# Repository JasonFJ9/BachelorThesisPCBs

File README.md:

# BachelorThesisPCBs
PCBs from Bachelor Thesis

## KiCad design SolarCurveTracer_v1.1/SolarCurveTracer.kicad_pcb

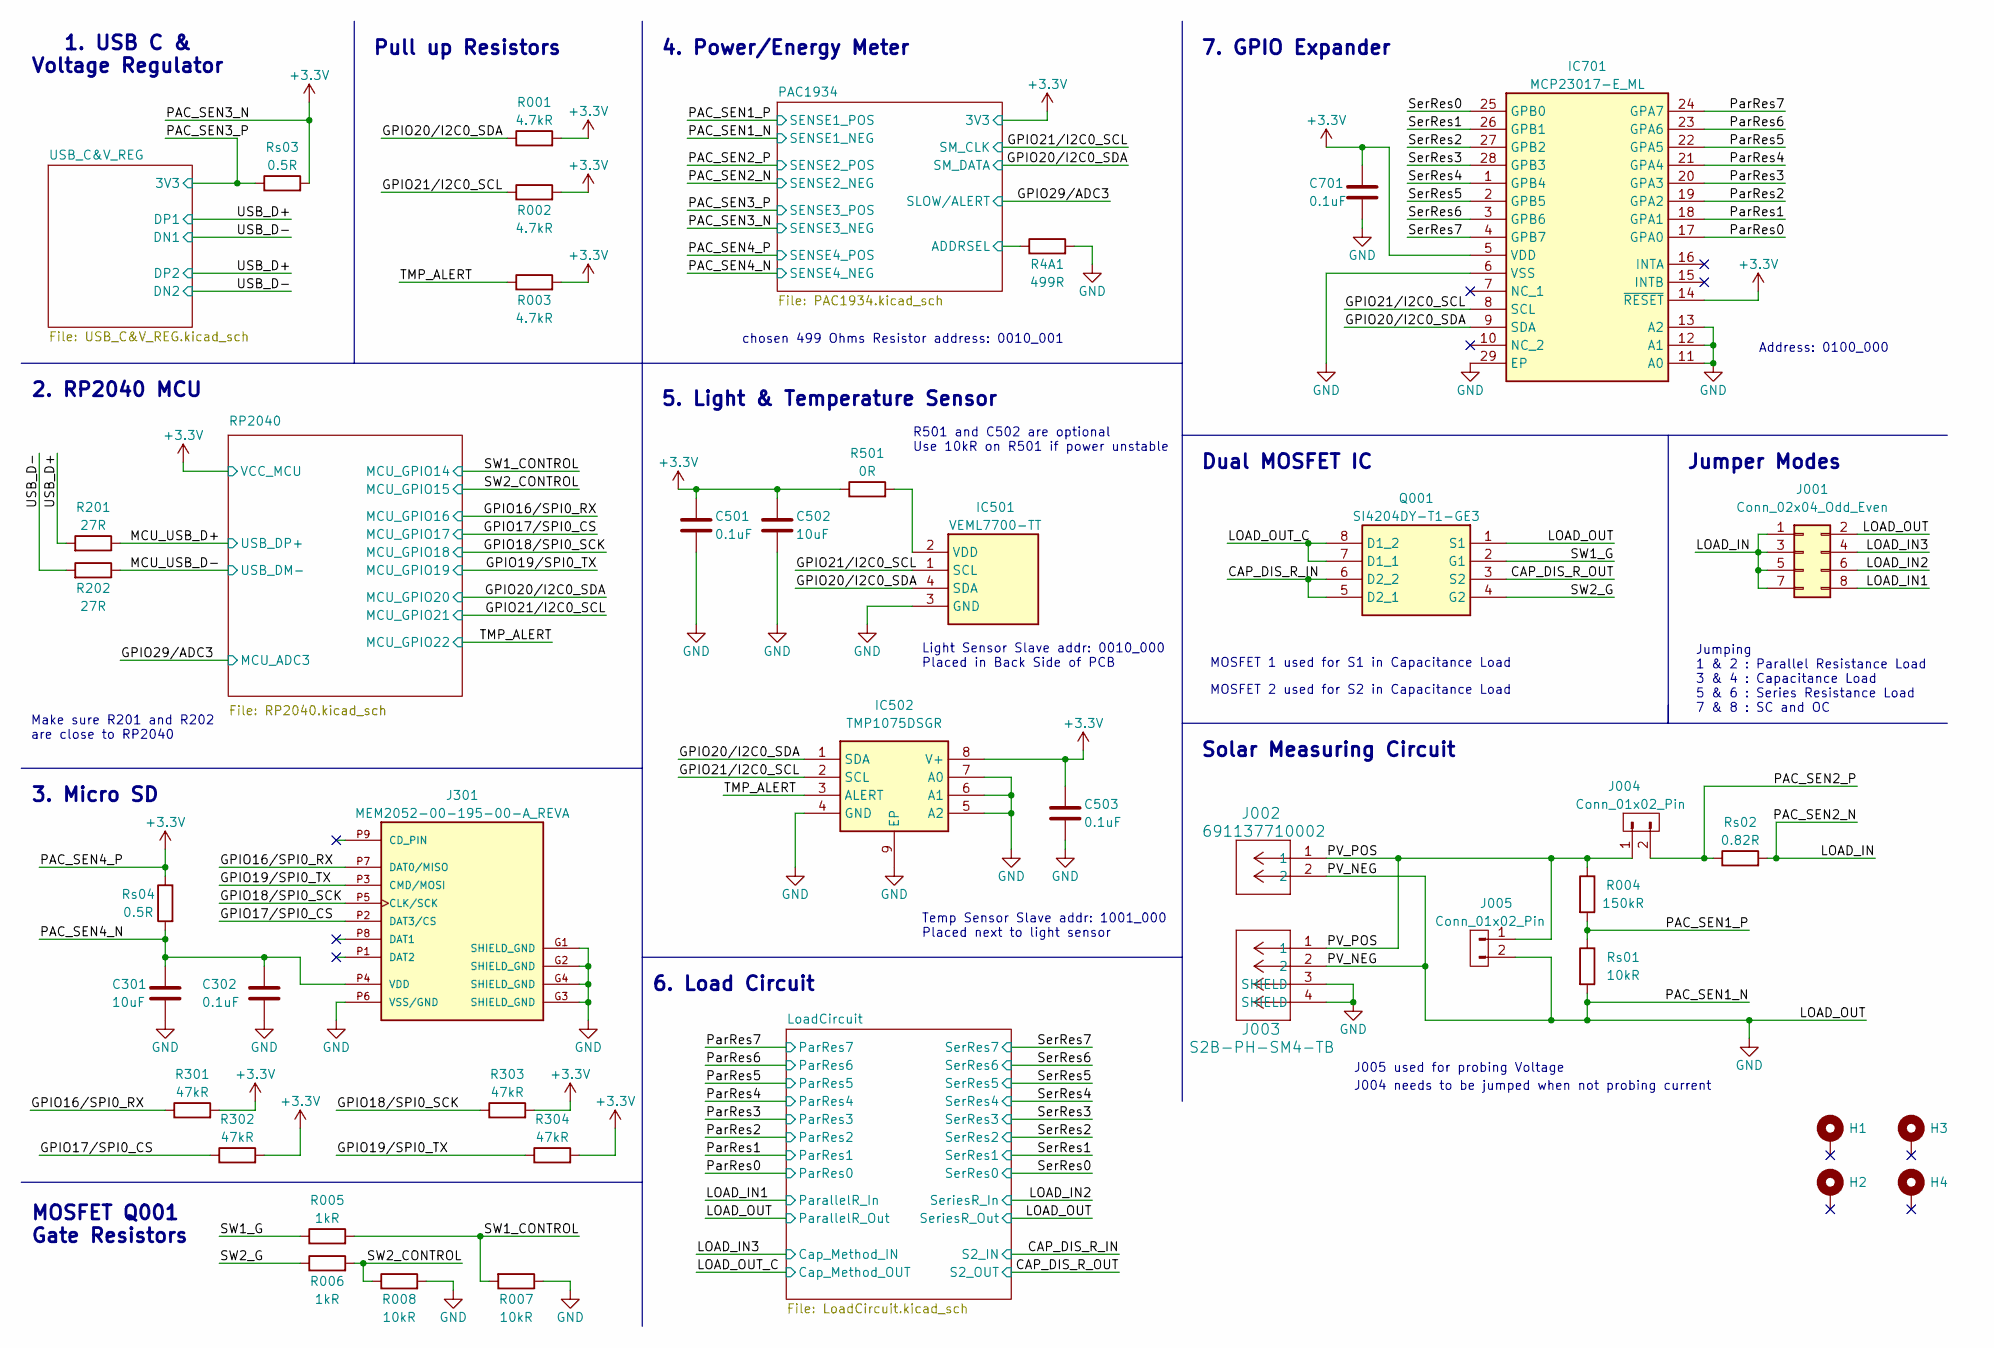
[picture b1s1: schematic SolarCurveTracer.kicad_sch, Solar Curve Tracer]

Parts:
C301, C502: 10uF; C_0603_1608Metric
C302, C501, C701: 0.1uF; C_0603_1608Metric
C503: 0.1uF; C_0402_1005Metric
H1, H2, H3, H4: MountingHole_Pad; MountingHole_3.2mm_M3_Pad
IC501: VEML7700-TT; VEML7700; Mouser Part Number 78-VEML7700-TT
IC502: TMP1075DSGR; SON50P200X200X80-9N; Mouser Part Number 595-TMP1075DSGR
IC701: MCP23017-E_ML; QFN65P600X600X100-29N-D; Mouser Part Number 579-MCP23017-E/ML
J001: Conn_02x04_Odd_Even; PinHeader_2x04_P2.54mm_Vertical
J002: 691137710002; CONN2_710002_WRE
J003: S2B-PH-SM4-TB; CONN_S2B-PH-SM4-TB_JST
J004, J005: Conn_01x02_Pin; PinHeader_1x02_P2.54mm_Vertical
J301: MEM2052-00-195-00-A_REVA; GCT_MEM2052-00-195-00-A_REVA; PARTREV A
Q001: SI4204DY-T1-GE3; SOIC127P600X175-8N; Mouser Part Number 781-SI4204DY-T1-GE3
R001, R002, R003: 4.7kR; R_0402_1005Metric
R004: 150kR; R_0603_1608Metric
R4A1: 499R; R_0603_1608Metric
R005, R006: 1kR; R_0402_1005Metric
R007, R008: 10kR; R_0402_1005Metric
R201, R202: 27R; R_0402_1005Metric
R301, R302, R303, R304: 47kR; R_0603_1608Metric
R501: 0R; R_0603_1608Metric
Rs01: 10kR; R_0805_2012Metric
Rs02: 0.82R; R_0805_2012Metric
Rs03, Rs04: 0.5R; R_0805_2012Metric

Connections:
+3.3V: C501.1, C502.1, C503.1, C701.1, IC502.8 (V+), IC701.5 (VDD), IC701.14 (~RESET), R001.2, R002.2, R003.2, R301.2, R302.2, R303.2, R304.2, R501.1, Rs03.2, Rs04.1; also elsewhere on the board
/CAP_DIS_R_IN: Q001.5 (D2_1), Q001.6 (D2_2); also elsewhere on the board
/CAP_DIS_R_OUT: Q001.3 (S2), Q001.7 (D1_1), Q001.8 (D1_2); also elsewhere on the board
/GPIO16/SPI0_RX: J301.P7 (DAT0/MISO), R301.1; also elsewhere on the board
/GPIO17/SPI0_CS: J301.P2 (DAT3/CS), R302.1; also elsewhere on the board
/GPIO18/SPI0_SCK: J301.P5 (CLK/SCK), R303.1; also elsewhere on the board
/GPIO19/SPI0_TX: J301.P3 (CMD/MOSI), R304.1; also elsewhere on the board
/GPIO20/I2C0_SDA: IC501.4 (SDA), IC502.1 (SDA), IC701.9 (SDA), R001.1; also elsewhere on the board
/GPIO21/I2C0_SCL: IC501.1 (SCL), IC502.2 (SCL), IC701.8 (SCL), R002.1; also elsewhere on the board
/LOAD_IN: J001.1, J001.3, J001.5, J001.7, Rs02.2; also elsewhere on the board
/LOAD_IN1: J001.8; also elsewhere on the board
/LOAD_IN2: J001.6; also elsewhere on the board
/LOAD_IN3: J001.4; also elsewhere on the board
/MCU_USB_D+: R201.1; also elsewhere on the board
/MCU_USB_D-: R202.1; also elsewhere on the board
/PAC1934/ADDRSEL: R4A1.1; also elsewhere on the board
/PAC_SEN1_P: R004.2, Rs01.1; also elsewhere on the board
/PAC_SEN2_P: J004.2, Rs02.1; also elsewhere on the board
/PAC_SEN3_P: Rs03.1; also elsewhere on the board
/PAC_SEN4_N: C301.1, C302.1, J301.P4 (VDD), Rs04.2; also elsewhere on the board
/PV_POS: J002.1, J003.1, J004.1, J005.1, R004.1
/ParRes0: IC701.17 (GPA0); also elsewhere on the board
/ParRes1: IC701.18 (GPA1); also elsewhere on the board
/ParRes2: IC701.19 (GPA2); also elsewhere on the board
/ParRes3: IC701.20 (GPA3); also elsewhere on the board
/ParRes4: IC701.21 (GPA4); also elsewhere on the board
/ParRes5: IC701.22 (GPA5); also elsewhere on the board
/ParRes6: IC701.23 (GPA6); also elsewhere on the board
/ParRes7: IC701.24 (GPA7); also elsewhere on the board
/SW1_CONTROL: R005.2, R007.2; also elsewhere on the board
/SW1_G: Q001.2 (G1), R005.1
/SW2_CONTROL: R006.2, R008.1; also elsewhere on the board
/SW2_G: Q001.4 (G2), R006.1
/SerRes0: IC701.25 (GPB0); also elsewhere on the board
/SerRes1: IC701.26 (GPB1); also elsewhere on the board
/SerRes2: IC701.27 (GPB2); also elsewhere on the board
/SerRes3: IC701.28 (GPB3); also elsewhere on the board
/SerRes4: IC701.1 (GPB4); also elsewhere on the board
/SerRes5: IC701.2 (GPB5); also elsewhere on the board
/SerRes6: IC701.3 (GPB6); also elsewhere on the board
/SerRes7: IC701.4 (GPB7); also elsewhere on the board
/TMP_ALERT: IC502.3 (ALERT), R003.1; also elsewhere on the board
/USB_D+: R201.2; also elsewhere on the board
/USB_D-: R202.2; also elsewhere on the board
GND: C301.2, C302.2, C501.2, C502.2, C503.2, C701.2, IC501.3 (GND), IC502.4 (GND), IC502.5 (A2), IC502.6 (A1), IC502.7 (A0), IC502.9 (EP), IC701.6 (VSS), IC701.11 (A0), IC701.12 (A1), IC701.13 (A2), IC701.29 (EP), J001.2, J002.2, J003.2, J003.3 (SHIELD), J003.4 (SHIELD), J005.2, J301.G1 (SHIELD_GND), J301.G2 (SHIELD_GND), J301.G3 (SHIELD_GND), J301.G4 (SHIELD_GND), J301.P6 (VSS/GND), Q001.1 (S1), R4A1.2, R007.1, R008.2, Rs01.2; also elsewhere on the board
unnamed: IC501.2 (VDD), R501.2

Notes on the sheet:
Jumper Modes
7. GPIO Expander
5. Light & Temperature Sensor
3. Micro SD
Solar Measuring Circuit
MOSFET 2 used for S2 in Capacitance Load
Dual MOSFET IC
Temp Sensor Slave addr: 1001_000 Placed next to light sensor
J005 used for probing Voltage
Make sure R201 and R202 are close to RP2040
Pull up Resistors
6. Load Circuit
R501 and C502 are optional Use 10kR on R501 if power unstable
1. USB C & Voltage Regulator
MOSFET Q001 Gate Resistors
2. RP2040 MCU
Light Sensor Slave addr: 0010_000 Placed in Back Side of PCB
MOSFET 1 used for S1 in Capacitance Load
chosen 499 Ohms Resistor address: 0010_001
J004 needs to be jumped when not probing current
Address: 0100_000
4. Power/Energy Meter
Jumping 1 & 2 : Parallel Resistance Load 3 & 4 : Capacitance Load 5 & 6 : Series Resistance Load 7 & 8 : SC and OC

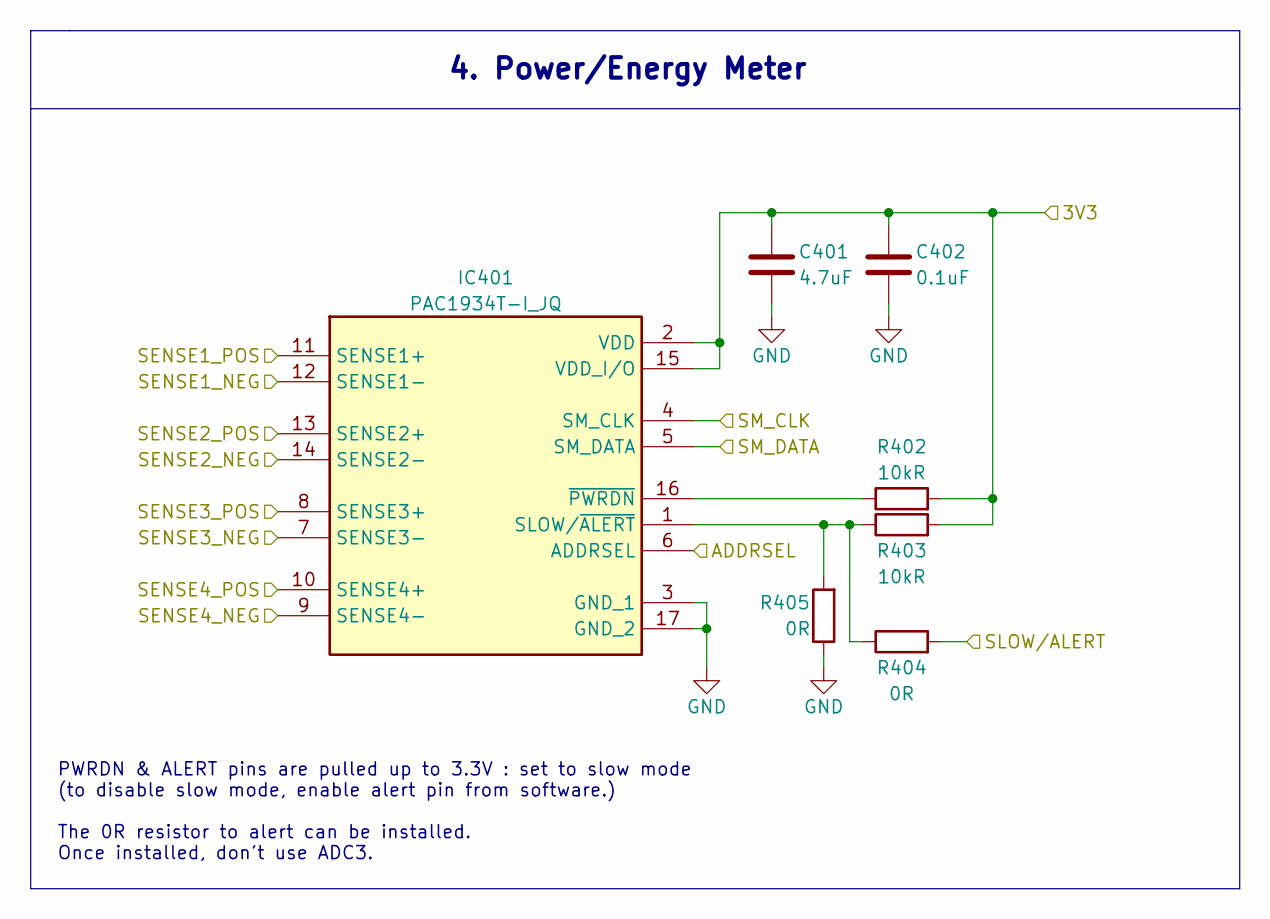
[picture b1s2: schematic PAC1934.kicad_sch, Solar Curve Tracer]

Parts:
C401: 4.7uF; C_0603_1608Metric
C402: 0.1uF; C_0603_1608Metric
IC401: PAC1934T-I_JQ; QFN65P400X400X55-17N-D; Mouser Part Number 579-PAC1934JQ
R402, R403: 10kR; R_0603_1608Metric
R404, R405: 0R; R_0603_1608Metric

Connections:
+3.3V: C401.1, C402.1, IC401.2 (VDD), IC401.7 (SENSE3-), IC401.10 (SENSE4+), IC401.15 (VDD_I/O), R402.2, R403.2; also elsewhere on the board
/GPIO20/I2C0_SDA: IC401.5 (SM_DATA); also elsewhere on the board
/GPIO21/I2C0_SCL: IC401.4 (SM_CLK); also elsewhere on the board
/GPIO29/ADC3: R404.2; also elsewhere on the board
/LOAD_IN: IC401.14 (SENSE2-); also elsewhere on the board
/PAC1934/ADDRSEL: IC401.6 (ADDRSEL); also elsewhere on the board
/PAC_SEN1_P: IC401.11 (SENSE1+); also elsewhere on the board
/PAC_SEN2_P: IC401.13 (SENSE2+); also elsewhere on the board
/PAC_SEN3_P: IC401.8 (SENSE3+); also elsewhere on the board
/PAC_SEN4_N: IC401.9 (SENSE4-); also elsewhere on the board
GND: C401.2, C402.2, IC401.3 (GND_1), IC401.12 (SENSE1-), IC401.17 (GND_2), R405.1; also elsewhere on the board
unnamed: IC401.1 (SLOW/~ALERT), R403.1, R404.1, R405.2
unnamed: IC401.16 (~PWRDN), R402.1

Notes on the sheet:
PWRDN & ALERT pins are pulled up to 3.3V : set to slow mode (to disable slow mode, enable alert pin from software.) The 0R resistor to alert can be installed. Once installed, don't use ADC3.
4. Power/Energy Meter

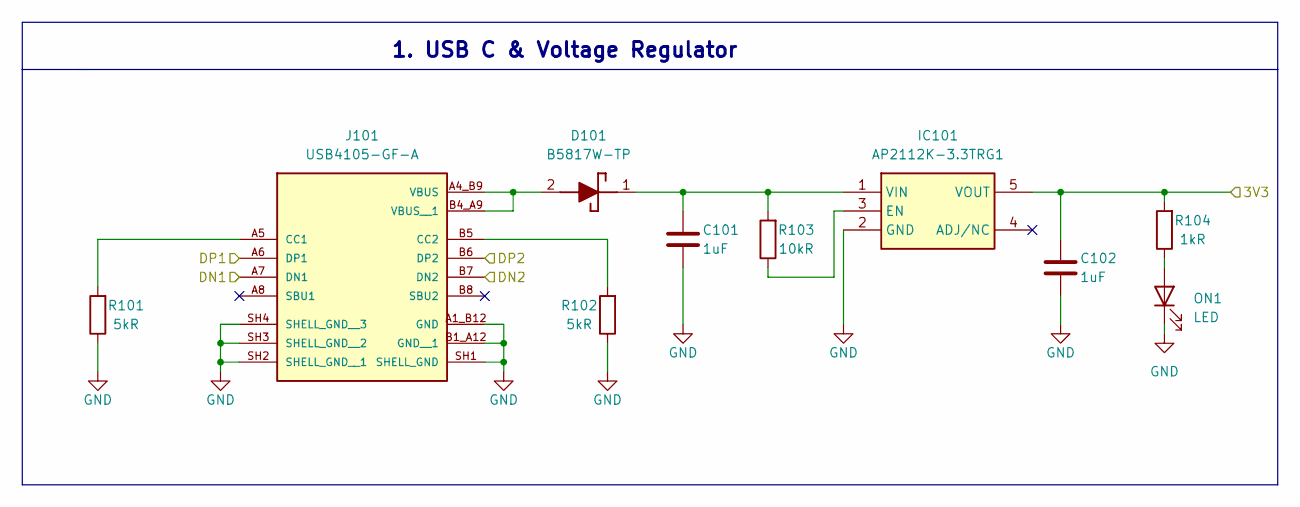
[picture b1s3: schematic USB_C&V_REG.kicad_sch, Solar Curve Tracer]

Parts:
C101, C102: 1uF; C_0603_1608Metric
D101: B5817W-TP; SOD3716X135N; Mouser Part Number 833-B5817W-TP
IC101: AP2112K-3.3TRG1; SOT95P282X130-5N; Mouser Part Number 621-AP2112K-3.3TRG1
J101: USB4105-GF-A; GCT_USB4105-GF-A; PARTREV B3
ON1: LED; LED_0603_1608Metric
R101, R102: 5kR; R_0603_1608Metric
R103: 10kR; R_0603_1608Metric
R104: 1kR; R_0603_1608Metric

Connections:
/PAC_SEN3_P: C102.1, IC101.5 (VOUT), R104.2; also elsewhere on the board
/USB_D+: J101.A6 (DP1), J101.B6 (DP2); also elsewhere on the board
/USB_D-: J101.A7 (DN1), J101.B7 (DN2); also elsewhere on the board
GND: C101.2, C102.2, IC101.2 (GND), J101.A1_B12 (GND), J101.B1_A12 (GND__1), J101.SH1 (SHELL_GND), J101.SH2 (SHELL_GND__1), J101.SH3 (SHELL_GND__2), J101.SH4 (SHELL_GND__3), ON1.1 (K), R101.1, R102.1; also elsewhere on the board
unnamed: D101.2 (A), J101.A4_B9 (VBUS), J101.B4_A9 (VBUS__1)
unnamed: C101.1, D101.1 (K), IC101.1 (VIN), R103.2
unnamed: IC101.3 (EN), R103.1
unnamed: J101.A5 (CC1), R101.2
unnamed: J101.B5 (CC2), R102.2
unnamed: ON1.2 (A), R104.1

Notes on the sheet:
1. USB C & Voltage Regulator

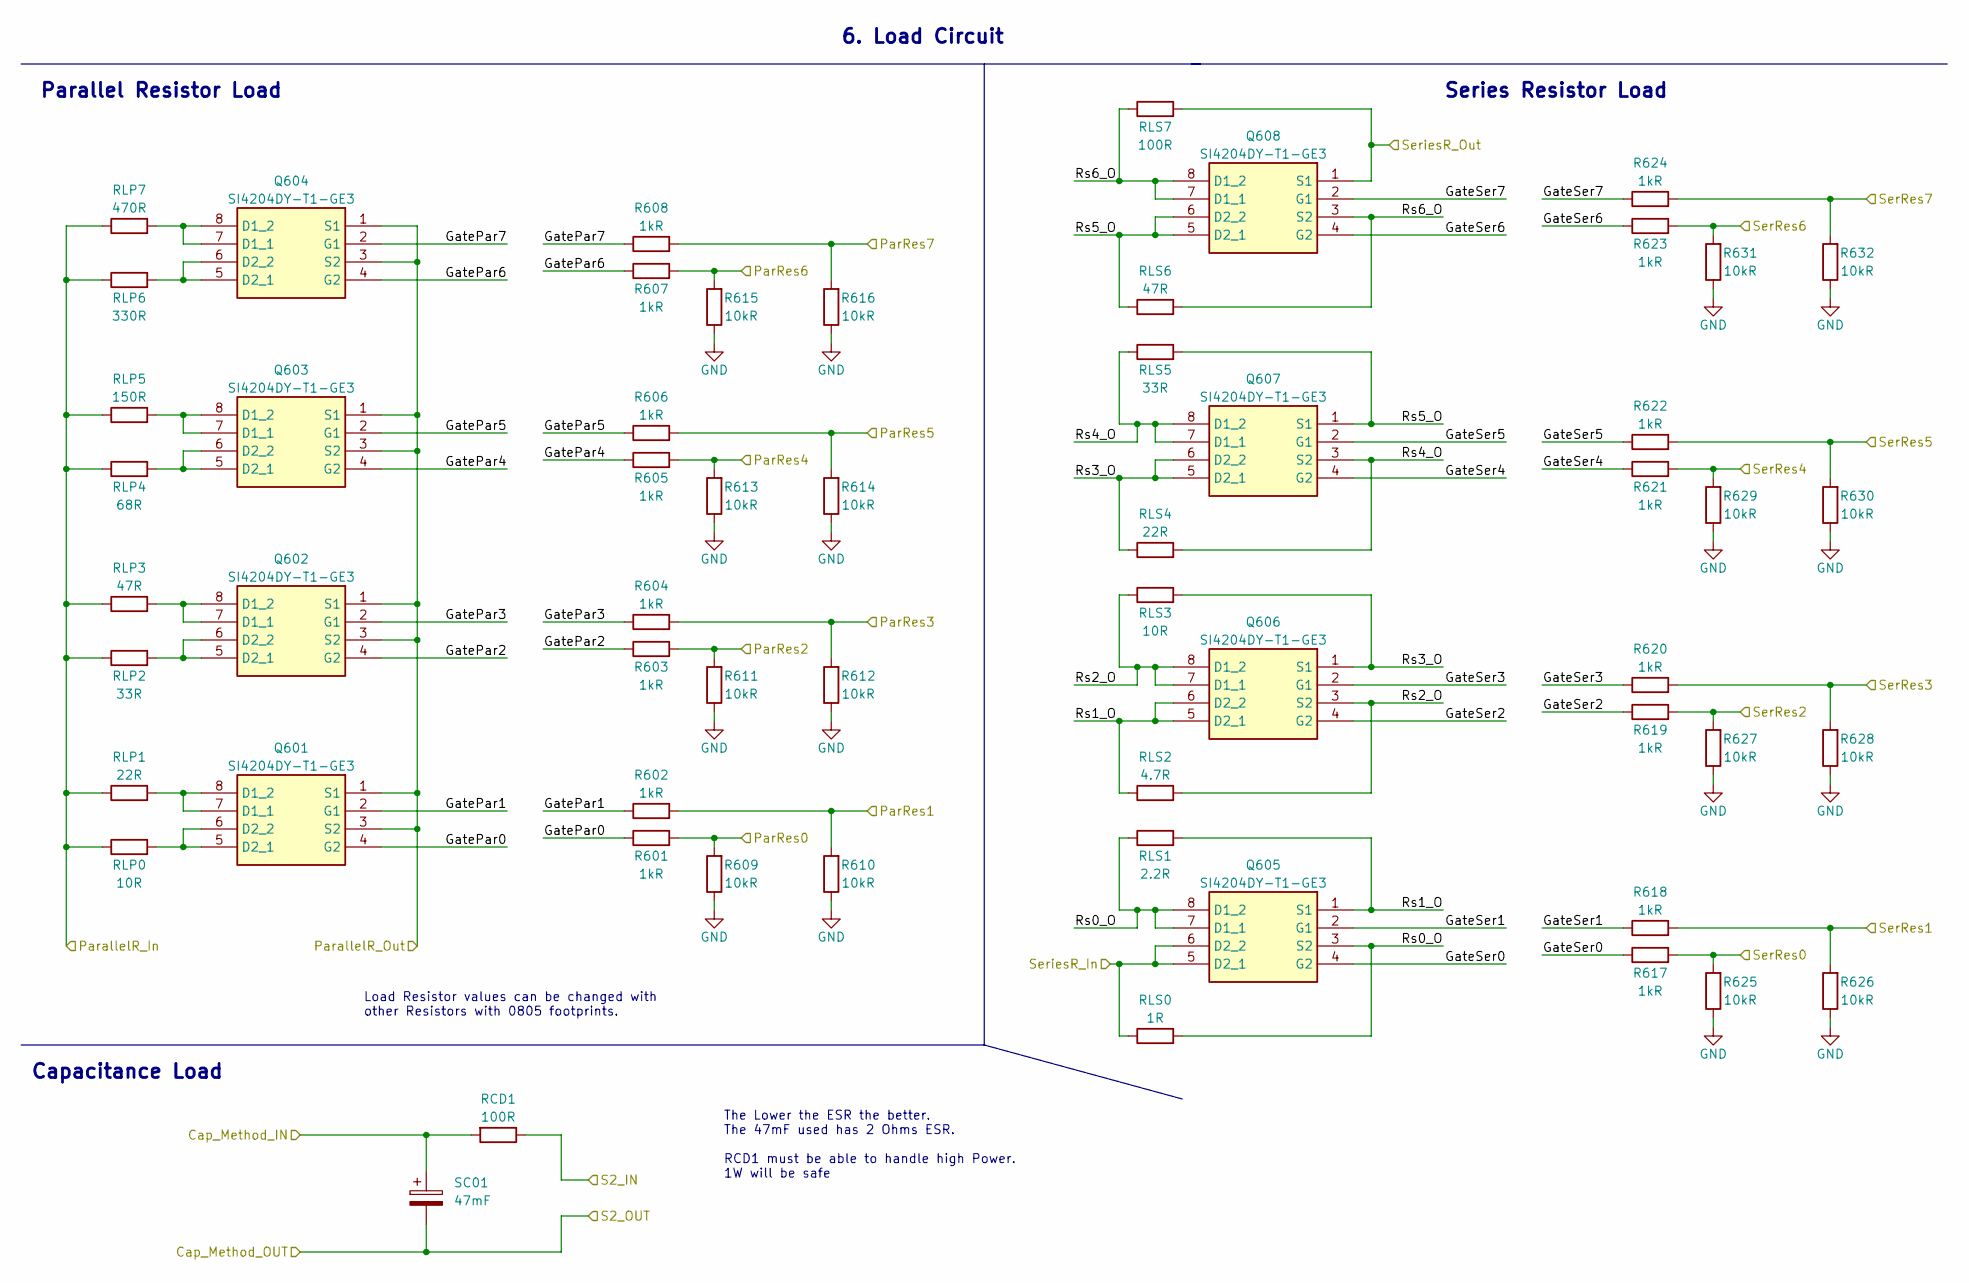
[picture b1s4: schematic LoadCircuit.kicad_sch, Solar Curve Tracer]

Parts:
Q601, Q602, Q603, Q604, Q605, Q606, Q607, Q608: SI4204DY-T1-GE3; SOIC127P600X175-8N; Mouser Part Number 781-SI4204DY-T1-GE3
R601, R602, R603, R604, R605, R606, R607, R608, R617, R618, R619, R620, R621, R622, R623, R624: 1kR; R_0402_1005Metric
R609, R610, R611, R612, R613, R614, R615, R616, R625, R626, R627, R628, R629, R630, R631, R632: 10kR; R_0402_1005Metric
RCD1: 100R; R_0805_2012Metric
RLP0: 10R; R_0805_2012Metric
RLP1: 22R; R_0805_2012Metric
RLP2: 33R; R_0805_2012Metric
RLP3: 47R; R_0805_2012Metric
RLP4: 68R; R_0805_2012Metric
RLP5: 150R; R_0805_2012Metric
RLP6: 330R; R_0805_2012Metric
RLP7: 470R; R_0805_2012Metric
RLS0: 1R; R_0805_2012Metric
RLS1: 2.2R; R_0805_2012Metric
RLS2: 4.7R; R_0805_2012Metric
RLS3: 10R; R_0805_2012Metric
RLS4: 22R; R_0805_2012Metric
RLS5: 33R; R_0805_2012Metric
RLS6: 47R; R_0805_2012Metric
RLS7: 100R; R_0805_2012Metric
SC01: 47mF; Capacitor_Radial_D12mm_P6.8mm

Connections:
/CAP_DIS_R_IN: RCD1.1; also elsewhere on the board
/CAP_DIS_R_OUT: SC01.2; also elsewhere on the board
/LOAD_IN1: RLP0.1, RLP1.1, RLP2.1, RLP3.1, RLP4.1, RLP5.1, RLP6.1, RLP7.1; also elsewhere on the board
/LOAD_IN2: Q605.5 (D2_1), Q605.6 (D2_2), RLS0.1; also elsewhere on the board
/LOAD_IN3: RCD1.2, SC01.1; also elsewhere on the board
/LoadCircuit/GatePar0: Q601.4 (G2), R601.1
/LoadCircuit/GatePar1: Q601.2 (G1), R602.1
/LoadCircuit/GatePar2: Q602.4 (G2), R603.1
/LoadCircuit/GatePar3: Q602.2 (G1), R604.1
/LoadCircuit/GatePar4: Q603.4 (G2), R605.1
/LoadCircuit/GatePar5: Q603.2 (G1), R606.1
/LoadCircuit/GatePar6: Q604.4 (G2), R607.1
/LoadCircuit/GatePar7: Q604.2 (G1), R608.1
/LoadCircuit/GateSer0: Q605.4 (G2), R617.1
/LoadCircuit/GateSer1: Q605.2 (G1), R618.1
/LoadCircuit/GateSer2: Q606.4 (G2), R619.1
/LoadCircuit/GateSer3: Q606.2 (G1), R620.1
/LoadCircuit/GateSer4: Q607.4 (G2), R621.1
/LoadCircuit/GateSer5: Q607.2 (G1), R622.1
/LoadCircuit/GateSer6: Q608.4 (G2), R623.1
/LoadCircuit/GateSer7: Q608.2 (G1), R624.1
/LoadCircuit/Rs0_O: Q605.3 (S2), Q605.7 (D1_1), Q605.8 (D1_2), RLS0.2, RLS1.1
/LoadCircuit/Rs1_O: Q605.1 (S1), Q606.5 (D2_1), Q606.6 (D2_2), RLS1.2, RLS2.1
/LoadCircuit/Rs2_O: Q606.3 (S2), Q606.7 (D1_1), Q606.8 (D1_2), RLS2.2, RLS3.1
/LoadCircuit/Rs3_O: Q606.1 (S1), Q607.5 (D2_1), Q607.6 (D2_2), RLS3.2, RLS4.1
/LoadCircuit/Rs4_O: Q607.3 (S2), Q607.7 (D1_1), Q607.8 (D1_2), RLS4.2, RLS5.1
/LoadCircuit/Rs5_O: Q607.1 (S1), Q608.5 (D2_1), Q608.6 (D2_2), RLS5.2, RLS6.1
/LoadCircuit/Rs6_O: Q608.3 (S2), Q608.7 (D1_1), Q608.8 (D1_2), RLS6.2, RLS7.1
/ParRes0: R601.2, R609.2; also elsewhere on the board
/ParRes1: R602.2, R610.2; also elsewhere on the board
/ParRes2: R603.2, R611.2; also elsewhere on the board
/ParRes3: R604.2, R612.2; also elsewhere on the board
/ParRes4: R605.2, R613.2; also elsewhere on the board
/ParRes5: R606.2, R614.2; also elsewhere on the board
/ParRes6: R607.2, R615.2; also elsewhere on the board
/ParRes7: R608.2, R616.2; also elsewhere on the board
/SerRes0: R617.2, R625.2; also elsewhere on the board
/SerRes1: R618.2, R626.2; also elsewhere on the board
/SerRes2: R619.2, R627.2; also elsewhere on the board
/SerRes3: R620.2, R628.2; also elsewhere on the board
/SerRes4: R621.2, R629.2; also elsewhere on the board
/SerRes5: R622.2, R630.2; also elsewhere on the board
/SerRes6: R623.2, R631.2; also elsewhere on the board
/SerRes7: R624.2, R632.2; also elsewhere on the board
GND: Q601.1 (S1), Q601.3 (S2), Q602.1 (S1), Q602.3 (S2), Q603.1 (S1), Q603.3 (S2), Q604.1 (S1), Q604.3 (S2), Q608.1 (S1), R609.1, R610.1, R611.1, R612.1, R613.1, R614.1, R615.1, R616.1, R625.1, R626.1, R627.1, R628.1, R629.1, R630.1, R631.1, R632.1, RLS7.2; also elsewhere on the board
unnamed: Q601.7 (D1_1), Q601.8 (D1_2), RLP1.2
unnamed: Q601.5 (D2_1), Q601.6 (D2_2), RLP0.2
unnamed: Q602.7 (D1_1), Q602.8 (D1_2), RLP3.2
unnamed: Q602.5 (D2_1), Q602.6 (D2_2), RLP2.2
unnamed: Q603.7 (D1_1), Q603.8 (D1_2), RLP5.2
unnamed: Q603.5 (D2_1), Q603.6 (D2_2), RLP4.2
unnamed: Q604.7 (D1_1), Q604.8 (D1_2), RLP7.2
unnamed: Q604.5 (D2_1), Q604.6 (D2_2), RLP6.2

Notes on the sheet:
Parallel Resistor Load
The Lower the ESR the better. The 47mF used has 2 Ohms ESR. RCD1 must be able to handle high Power. 1W will be safe
6. Load Circuit
Load Resistor values can be changed with other Resistors with 0805 footprints.
Series Resistor Load
Capacitance Load

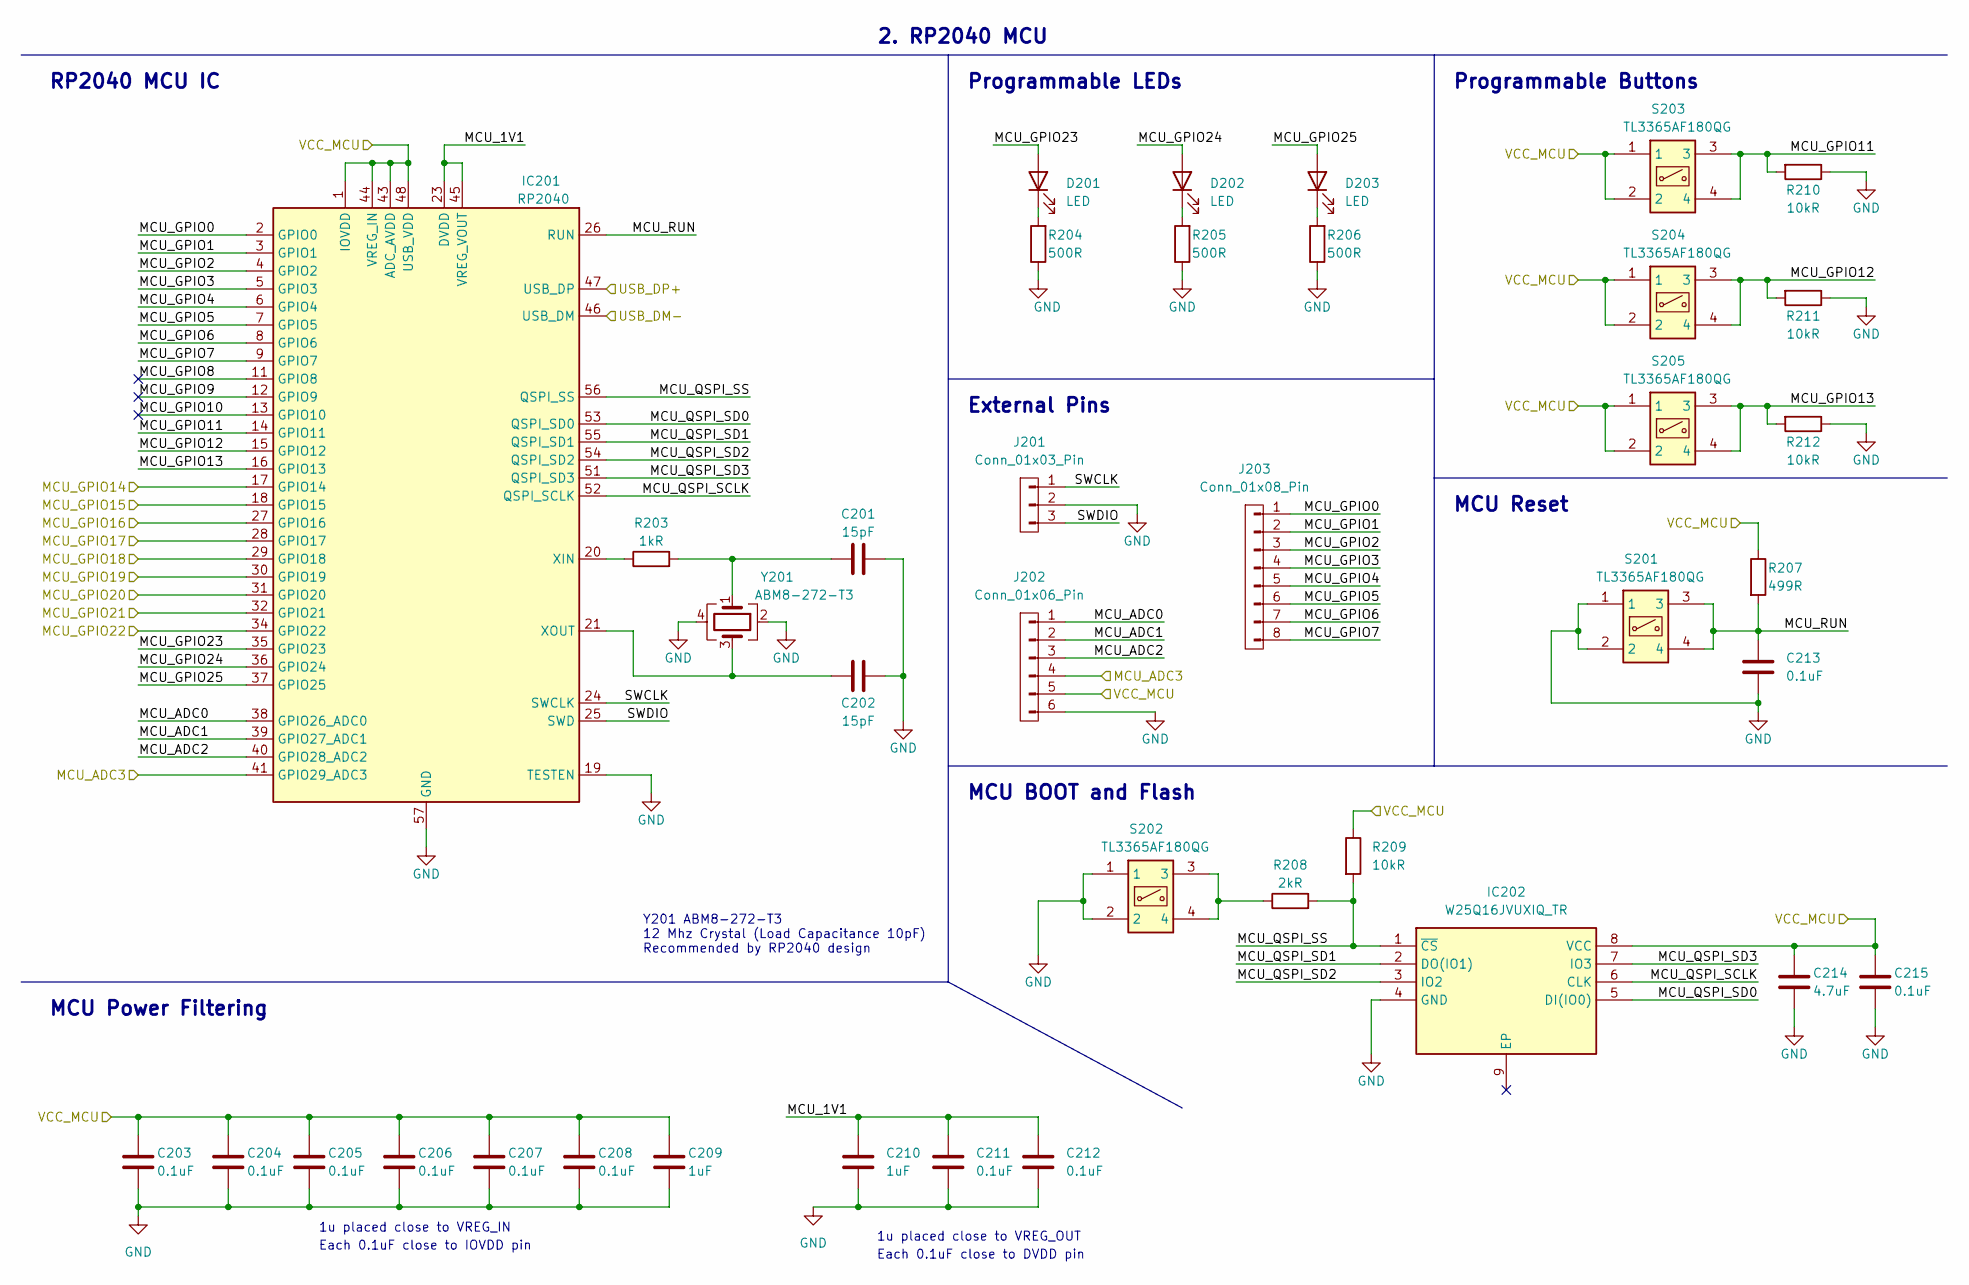
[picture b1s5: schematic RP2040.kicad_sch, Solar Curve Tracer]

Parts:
C201, C202: 15pF; C_0402_1005Metric
C203, C204, C205, C206, C207, C208, C211, C212, C213, C215: 0.1uF; C_0402_1005Metric
C209, C210: 1uF; C_0402_1005Metric
C214: 4.7uF; C_0402_1005Metric
D201, D202, D203: LED; LED_0402_1005Metric
IC201: RP2040; QFN-56-1EP_7x7mm_P0.4mm_EP3.2x3.2mm
IC202: W25Q16JVUXIQ_TR; SON50P300X200X60-9N; Mouser Part Number 454-W25Q16JVUXIQTR
J201: Conn_01x03_Pin; PinSocket_1x03_P2.54mm_Vertical
J202: Conn_01x06_Pin; PinSocket_1x06_P2.54mm_Vertical
J203: Conn_01x08_Pin; PinSocket_1x08_P2.54mm_Vertical
R203: 1kR; R_0402_1005Metric
R204, R205, R206: 500R; R_0402_1005Metric
R207: 499R; R_0402_1005Metric
R208: 2kR; R_0402_1005Metric
R209, R210, R211, R212: 10kR; R_0402_1005Metric
S201, S202, S203, S204, S205: TL3365AF180QG; Mouser Part Number 612-TL3365AF180QG
Y201: ABM8-272-T3; ABM8272T3

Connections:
+3.3V: C203.1, C204.1, C205.1, C206.1, C207.1, C208.1, C209.1, C214.1, C215.1, IC201.1 (IOVDD), IC201.10 (IOVDD), IC201.22 (IOVDD), IC201.33 (IOVDD), IC201.42 (IOVDD), IC201.43 (ADC_AVDD), IC201.44 (VREG_IN), IC201.48 (USB_VDD), IC201.49 (IOVDD), IC202.8 (VCC), J202.5, R207.1, R209.1, S203.1, S203.2, S204.1, S204.2, S205.1, S205.2; also elsewhere on the board
/GPIO16/SPI0_RX: IC201.27 (GPIO16); also elsewhere on the board
/GPIO17/SPI0_CS: IC201.28 (GPIO17); also elsewhere on the board
/GPIO18/SPI0_SCK: IC201.29 (GPIO18); also elsewhere on the board
/GPIO19/SPI0_TX: IC201.30 (GPIO19); also elsewhere on the board
/GPIO20/I2C0_SDA: IC201.31 (GPIO20); also elsewhere on the board
/GPIO21/I2C0_SCL: IC201.32 (GPIO21); also elsewhere on the board
/GPIO29/ADC3: IC201.41 (GPIO29_ADC3), J202.4; also elsewhere on the board
/MCU_USB_D+: IC201.47 (USB_DP); also elsewhere on the board
/MCU_USB_D-: IC201.46 (USB_DM); also elsewhere on the board
/RP2040/MCU_1V1: C210.1, C211.1, C212.1, IC201.23 (DVDD), IC201.45 (VREG_VOUT), IC201.50 (DVDD)
/RP2040/MCU_ADC0: IC201.38 (GPIO26_ADC0), J202.1
/RP2040/MCU_ADC1: IC201.39 (GPIO27_ADC1), J202.2
/RP2040/MCU_ADC2: IC201.40 (GPIO28_ADC2), J202.3
/RP2040/MCU_GPIO0: IC201.2 (GPIO0), J203.1
/RP2040/MCU_GPIO1: IC201.3 (GPIO1), J203.2
/RP2040/MCU_GPIO2: IC201.4 (GPIO2), J203.3
/RP2040/MCU_GPIO3: IC201.5 (GPIO3), J203.4
/RP2040/MCU_GPIO4: IC201.6 (GPIO4), J203.5
/RP2040/MCU_GPIO5: IC201.7 (GPIO5), J203.6
/RP2040/MCU_GPIO6: IC201.8 (GPIO6), J203.7
/RP2040/MCU_GPIO7: IC201.9 (GPIO7), J203.8
/RP2040/MCU_GPIO8: IC201.11 (GPIO8)
/RP2040/MCU_GPIO9: IC201.12 (GPIO9)
/RP2040/MCU_GPIO10: IC201.13 (GPIO10)
/RP2040/MCU_GPIO11: IC201.14 (GPIO11), R210.2, S203.3, S203.4
/RP2040/MCU_GPIO12: IC201.15 (GPIO12), R211.2, S204.3, S204.4
/RP2040/MCU_GPIO13: IC201.16 (GPIO13), R212.2, S205.3, S205.4
/RP2040/MCU_GPIO23: D201.2 (A), IC201.35 (GPIO23)
/RP2040/MCU_GPIO24: D202.2 (A), IC201.36 (GPIO24)
/RP2040/MCU_GPIO25: D203.2 (A), IC201.37 (GPIO25)
/RP2040/MCU_QSPI_SCLK: IC201.52 (QSPI_SCLK), IC202.6 (CLK)
/RP2040/MCU_QSPI_SD0: IC201.53 (QSPI_SD0), IC202.5 (DI(IO0))
/RP2040/MCU_QSPI_SD1: IC201.55 (QSPI_SD1), IC202.2 (DO(IO1))
/RP2040/MCU_QSPI_SD2: IC201.54 (QSPI_SD2), IC202.3 (IO2)
/RP2040/MCU_QSPI_SD3: IC201.51 (QSPI_SD3), IC202.7 (IO3)
/RP2040/MCU_QSPI_SS: IC201.56 (QSPI_SS), IC202.1 (~CS), R208.2, R209.2
/RP2040/MCU_RUN: C213.1, IC201.26 (RUN), R207.2, S201.3, S201.4
/RP2040/SWCLK: IC201.24 (SWCLK), J201.1
/RP2040/SWDIO: IC201.25 (SWD), J201.3
/SW1_CONTROL: IC201.17 (GPIO14); also elsewhere on the board
/SW2_CONTROL: IC201.18 (GPIO15); also elsewhere on the board
/TMP_ALERT: IC201.34 (GPIO22); also elsewhere on the board
GND: C201.2, C202.2, C203.2, C204.2, C205.2, C206.2, C207.2, C208.2, C209.2, C210.2, C211.2, C212.2, C213.2, C214.2, C215.2, IC201.19 (TESTEN), IC201.57 (GND), IC202.4 (GND), J201.2, J202.6, R204.1, R205.1, R206.1, R210.1, R211.1, R212.1, S201.1, S201.2, S202.1, S202.2, Y201.2, Y201.4; also elsewhere on the board
unnamed: C201.1, R203.2, Y201.1
unnamed: D201.1 (K), R204.2
unnamed: D202.1 (K), R205.2
unnamed: D203.1 (K), R206.2
unnamed: IC201.20 (XIN), R203.1
unnamed: C202.1, IC201.21 (XOUT), Y201.3
unnamed: R208.1, S202.3, S202.4

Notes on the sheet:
1u placed close to VREG_IN
1u placed close to VREG_OUT
Each 0.1uF close to IOVDD pin
RP2040 MCU IC
MCU BOOT and Flash
MCU Power Filtering
Programmable Buttons
MCU Reset
Y201 ABM8-272-T3 12 Mhz Crystal (Load Capacitance 10pF) Recommended by RP2040 design
2. RP2040 MCU
Programmable LEDs
External Pins
Each 0.1uF close to DVDD pin
